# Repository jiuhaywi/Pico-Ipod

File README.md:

# The Pico 2W Music Player
The Raspberry Pi Pico 2W Music Player is a project based on the apple ipod - a handheld, battery-powered music player.

## Why Did I Create This Project?
> All of the current pocket music players on the market are either **stupidly expensive, bad quality, or low storage** with little to no room for upgrading. Due to this, I wanted to create such a project, creating my own handheld music player instead of using all my phone's battery on music. This project was also something interesting to get into, being my first ever hardware project.

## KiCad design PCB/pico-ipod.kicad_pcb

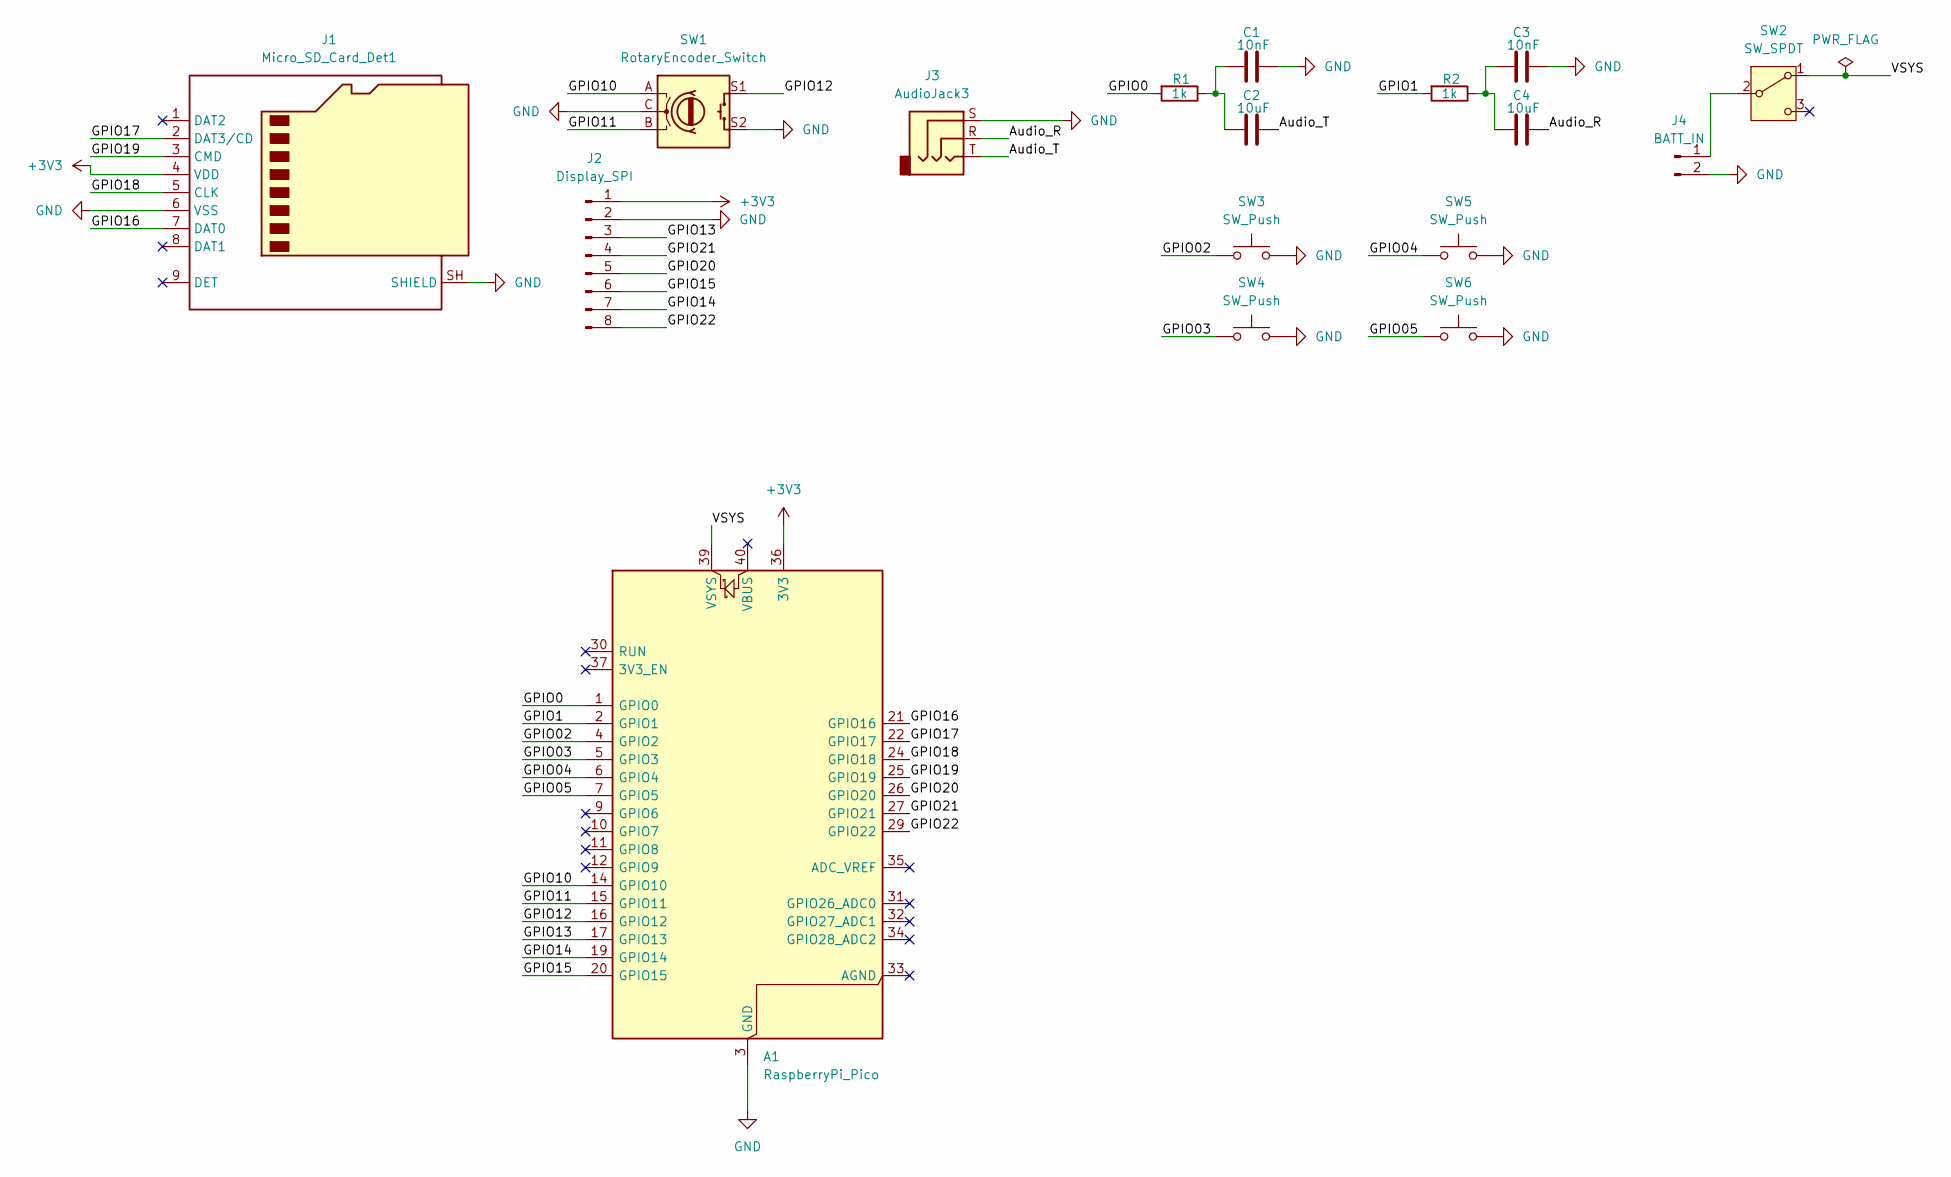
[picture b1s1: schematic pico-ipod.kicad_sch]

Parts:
A1: RaspberryPi_Pico; RaspberryPi_Pico_Common_Unspecified
C1, C3: 10nF; C_0805_2012Metric
C2, C4: 10uF; C_0805_2012Metric
J1: Micro_SD_Card_Det1; microSD_HC_Hirose_DM3AT-SF-PEJM5
J2: Display_SPI; PinHeader_1x08_P2.54mm_Vertical
J3: AudioJack3; Jack_3.5mm_CUI_SJ-3523-SMT_Horizontal
J4: BATT_IN; JST_PH_S2B-PH-K_1x02_P2.00mm_Horizontal
R1, R2: 1k; R_0805_2012Metric
SW1: RotaryEncoder_Switch; RotaryEncoder_Alps_EC11E-Switch_Vertical_H20mm
SW2: SW_SPDT; SW_Slide_SPDT_Straight_CK_OS102011MS2Q
SW3, SW4, SW5, SW6: SW_Push; SW_SPST_PTS645Sx43SMTR92

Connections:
+3V3: A1.36 (3V3), J1.4 (VDD), J2.1
/Audio_R: C4.2, J3.R
/Audio_T: C2.2, J3.T
/GPIO0: A1.1 (GPIO0), R1.2
/GPIO1: A1.2 (GPIO1), R2.2
/GPIO02: A1.4 (GPIO2), SW3.1
/GPIO03: A1.5 (GPIO3), SW4.1
/GPIO04: A1.6 (GPIO4), SW5.1
/GPIO05: A1.7 (GPIO5), SW6.1
/GPIO10: A1.14 (GPIO10), SW1.A
/GPIO11: A1.15 (GPIO11), SW1.B
/GPIO12: A1.16 (GPIO12), SW1.S1
/GPIO13: A1.17 (GPIO13), J2.3
/GPIO14: A1.19 (GPIO14), J2.7
/GPIO15: A1.20 (GPIO15), J2.6
/GPIO16: A1.21 (GPIO16), J1.7 (DAT0)
/GPIO17: A1.22 (GPIO17), J1.2 (DAT3/CD)
/GPIO18: A1.24 (GPIO18), J1.5 (CLK)
/GPIO19: A1.25 (GPIO19), J1.3 (CMD)
/GPIO20: A1.26 (GPIO20), J2.5
/GPIO21: A1.27 (GPIO21), J2.4
/GPIO22: A1.29 (GPIO22), J2.8
/VSYS: A1.39 (VSYS), SW2.1 (A)
GND: A1.3 (GND), A1.8 (GND), A1.13 (GND), A1.18 (GND), A1.23 (GND), A1.28 (GND), A1.38 (GND), C1.2, C3.2, J1.6 (VSS), J1.SH (SHIELD), J2.2, J3.S, J4.2, SW1.C, SW1.S2, SW3.2, SW4.2, SW5.2, SW6.2
unnamed: C1.1, C2.1, R1.1
unnamed: C3.1, C4.1, R2.1
unnamed: J4.1, SW2.2 (B)

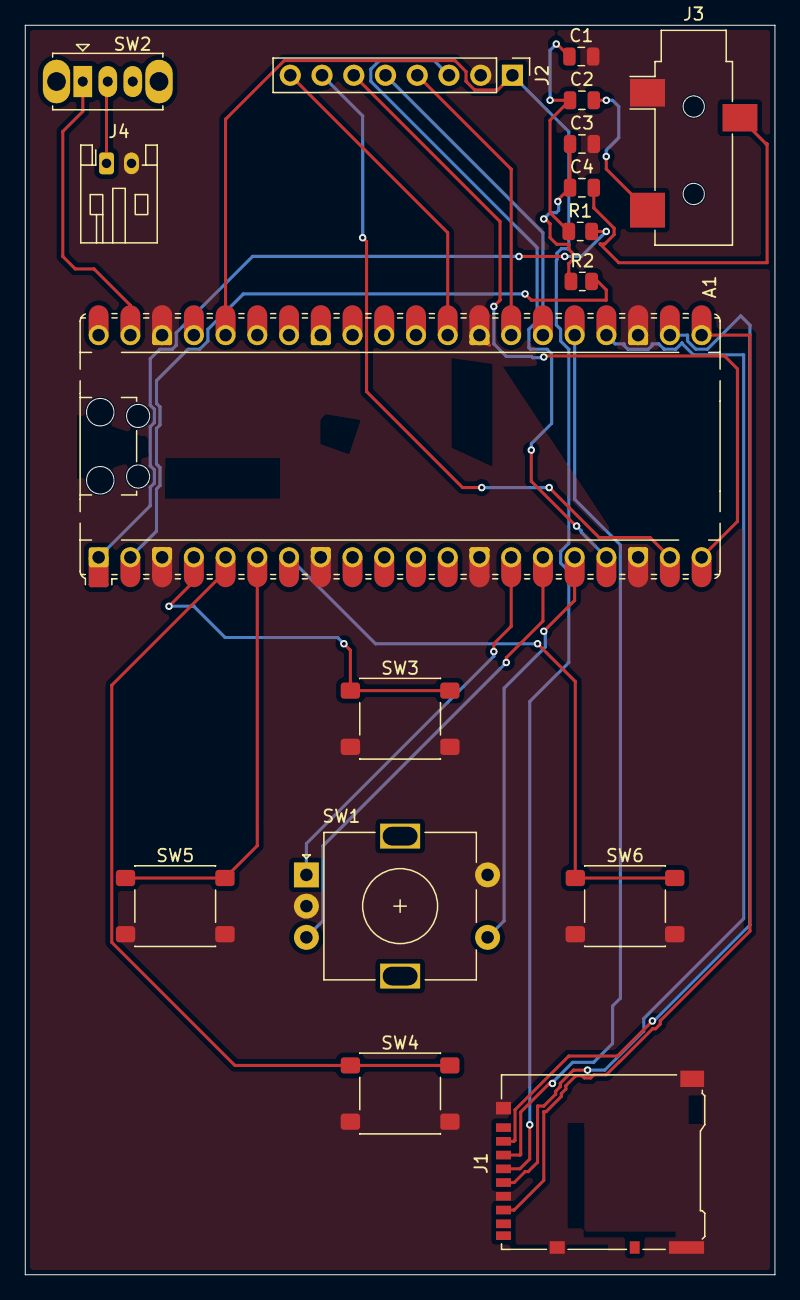
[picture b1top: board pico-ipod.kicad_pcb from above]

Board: 2 copper layers, 60.0 x 100.0 mm, 17 parts (0 on the bottom side), 27 nets.
